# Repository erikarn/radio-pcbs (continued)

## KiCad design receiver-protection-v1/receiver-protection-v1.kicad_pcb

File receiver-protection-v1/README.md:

# SDR RX receiver protection

## What is this?

This is a super simple project to provide some level of protection
of an SDR receiver.

It adds surge protection, signal level clamping diodes and defaults
to shorting the receiver input when the power isn't applied.

I designed this to be able to leave in front of SDRs which may be
located near transmit antennas.  No, this won't protect your
SDR against a directly connected transmitter - ie, it's not a TX/RX
switch! - but it provides similar levels of protection as your
solid state HF/VHF/UHF transceiver may have.

## How to use it

 * Hook the input side up to your antenna
 * Hook the output side up to your SDR
 * Apply 12v to the supply pin
 * When you want to receive, apply 12v to the RX_EN pin
 * When you don't want to receive, don't apply 12v to the RX_EN pin

## Building it

 * Populate almost all the parts!
 * You don't need to populate two surge protectors - populate the D5
   one (on the input side) as that'll protect things before the relay.
 * Be careful of the Q1 footprint - yes, it's a small one

## Building modifications

If you don't need the relay switch and you just want the protection,
you can short pin 7 and 12 on the relay footprint (K1) and only populate
the SMA connectors, surge protectors and diodes.

If you want it to always be on when you apply power, then just short
pins 1 and 2 on J3 so 12v always appears on the RX_EN pin.

I supplied surge protector footprints on both sides of the relay.
You don't necessarily need both; I added it in case I wanted to
experiment.

## Notes!

### Using it with a bias-tee

 * Don't use this with an SDR that is providing a bias-tee; since it
   grounds the SDR facing port when RX_EN isn't enabled, it'll just short
   your bias-tee.
 * If you want to use it with a bias-tee then you can either clip pin 10
   of your relay or scrape away the pad/track on pin 10 of K1.  That way
   the SDR isn't grounded when RX_EN is off, and thus the bias-tee power
   isn't shorted.

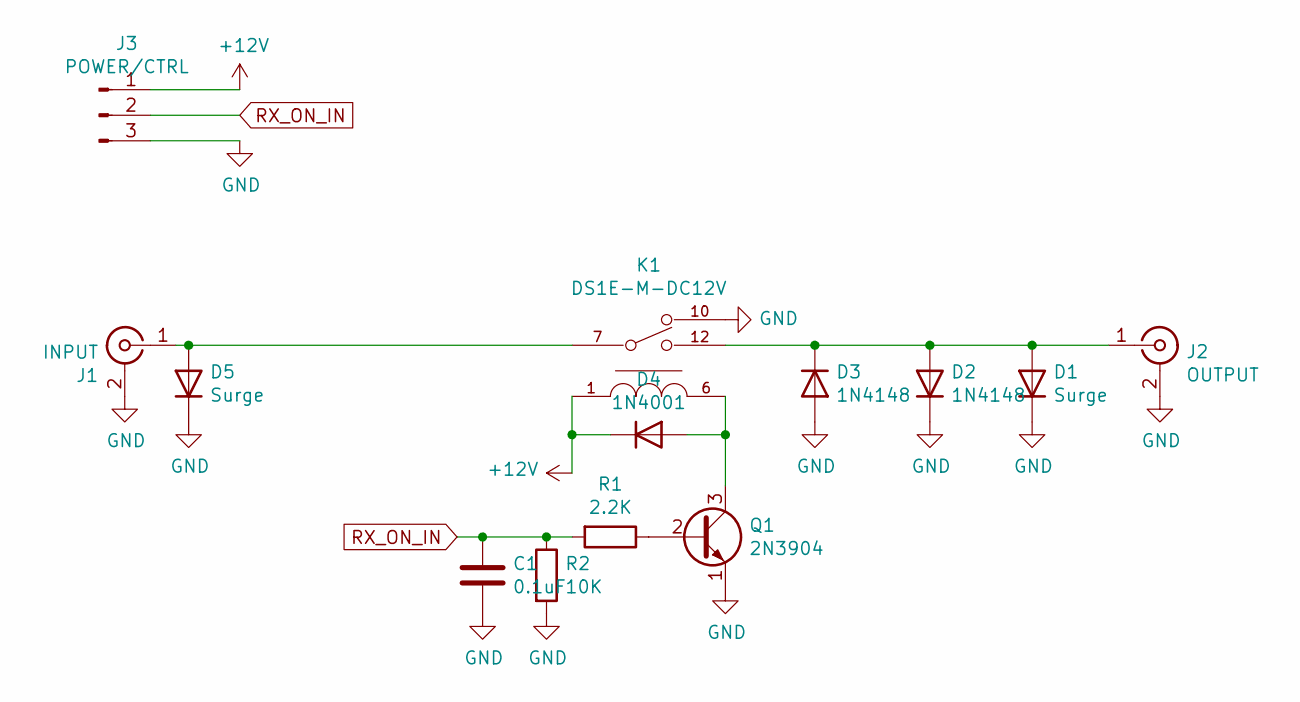
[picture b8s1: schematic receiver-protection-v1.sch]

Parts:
C1: 0.1uF; C_Disc_D3.8mm_W2.6mm_P2.50mm
D1, D5: Surge; D_DO-41_SOD81_P12.70mm_Horizontal
D2, D3: 1N4148; D_DO-35_SOD27_P7.62mm_Horizontal
D4: 1N4001; D_DO-41_SOD81_P12.70mm_Horizontal
J1: INPUT; SMA_Amphenol_132134-11_Vertical
J2: OUTPUT; SMA_Amphenol_132134-11_Vertical
J3: POWER/CTRL; PinHeader_1x03_P2.54mm_Vertical
K1: DS1E-M-DC12V; DIP-12_W7.62mm_Socket; current rating 3A; voltage rating AC 250V; mouser part number 769-DS1E-M-DC12V; digikey description RELAY GEN PURPOSE SPDT 2A 250V
Q1: 2N3904; TO-92_Inline
R1: 2.2K; R_Axial_DIN0207_L6.3mm_D2.5mm_P10.16mm_Horizontal
R2: 10K; R_Axial_DIN0207_L6.3mm_D2.5mm_P10.16mm_Horizontal

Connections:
+12V: D4.1 (K), J3.1, K1.1
GND: C1.2, D1.1 (K), D2.1 (K), D3.2 (A), D5.1 (K), J1.2 (Ext), J2.2 (Ext), J3.3, K1.10, Q1.1 (E), R2.2
unnamed: D1.2 (A), D2.2 (A), D3.1 (K), J2.1 (In), K1.12
unnamed: D4.2 (A), K1.6, Q1.3 (C)
unnamed: D5.2 (A), J1.1 (In), K1.7
unnamed: Q1.2 (B), R1.1
RX_ON_IN: C1.1, J3.2, R1.2, R2.1

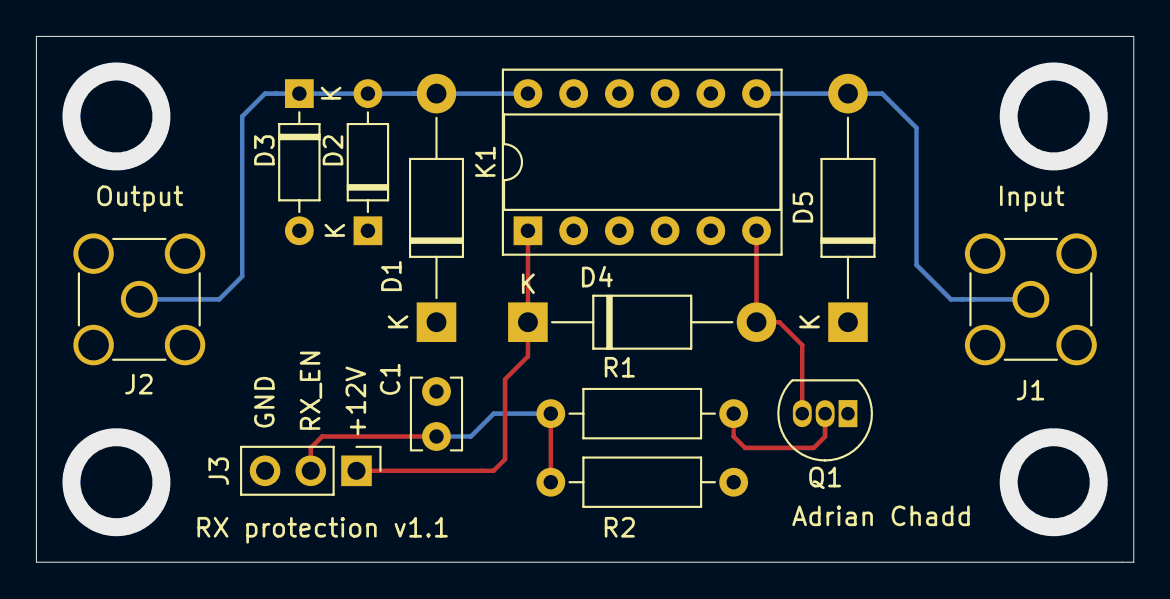
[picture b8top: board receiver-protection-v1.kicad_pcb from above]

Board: 2 copper layers, 61.0 x 29.2 mm, 13 parts (0 on the bottom side), 7 nets.

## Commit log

2020-09-14 Initial transverter control board prototype!
2020-09-22 ok, let's just put these in the top level
2020-09-22 Initial project - add basic receiver protection PCB.
    This is for protecting SDRs on receive antennas from being exposed
    whilst off, as well as some surge protection and signal-overload
    protection.
    I'll build it and sweep HF/VHF/UHF, see where it's useful.
2020-10-03 add revision 1.1 changes
    * make sure the mounting hole vias are attached to ground!
    * reverse input/output - make sure that the SDR facing output
    has the protection diodes and optional surge protector, and
    is grounded when the enable signal isn't applied
    * label input, output, power/ground/enable
    * add description, my name, and revision number
2020-10-03 v1.1 - whoops, annotate the schematic
2020-10-03 Add an initial readme!
2020-10-03 Add initial top-level readme
2020-11-16 initial coilcraft library thingy
2020-11-16 board for testing 630m filter designs
2020-11-16 WIP for ts-140 + pll-2001 PLL IC replacement adapter board
2020-11-16 WIP for a 630m TX/RX transverter control board - letting a TS-430S as a transverter control a 630m TX/RX path.
2020-12-11 Updates!
2020-12-12 Update PCB layout, it should work? kinda? we'll see.
2020-12-30 Whoops - my coil orientation/pinout was JUST PLAIN WRONG.
    So fix the schematic to do the right thing; I'll have to hack something on my
    development pcb to test that the filter actually works..
2020-12-31 more fixes:
    * missed ground plane ties for the signal connectors, whoops
    * add ground pins for the coils so they can be tied to ground
    * add label
2020-12-31 More v0.3 fixes -
    * fix the bloody signal routing for that middle IF coil, what was I thinking
    * don't use a cap to xverter-gnd; just tie them together and to ground
    That should be much better!
2021-01-13 * More layout fixes * Make the silk screen layer not actually terrible
2021-01-16 I got the fucking relay power backwards. WTAF.
2021-03-13 Add initial ubitx IF board design, from ubitx v6.
    This is aimed to be a copy of the dual direction IF amplifiers
    that are used in the ubitx radios. It's intended to be used
    as bidirectional IF amplifiers or two separate IF amplifiers.
    Anyway, this is the first bit.
2021-03-13 * whoops, use a proper ground * make txb/rxb a pair of pairs, in case they want to be wired/powered via two separate connections (ie, as independent IF amplifiers) rather than expecting TXB/RXB to be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
2021-03-14 * add net file * update an actual routed pcb, need to fix labels and put my name on it
2021-03-14 whoops! fix
2021-03-14 * Layout updates * Fix text labelling * Add my text bits here!
    This was sent to oshpark as 1.0 today for printing!
2021-03-15 WHOOPS - my last minute vias were err, wrong.
    THIS is now what's sent as v1.0 to print at oshpark!
2021-04-07 add component for the ubitx trifilar inductor they use.
2021-04-07 Add initial ubitx mixer/filter board.
    This is the mixer and filter stage used in each of the two conversion stages.
    My goal is that only the parts needed for a given stage are populated, rather
    than building two separate PCB layouts.
2021-06-12 Add initial unfinished apple-ii rom adapter thingy
2021-06-12 Incremental update! Maybe this'll work? :-)
2021-06-12 whoops, missed a connection!
2021-06-16 Initial cut (rev 0.1) of the 8t28 <-> 74ls245 adapter
2021-06-16 Move some silkscreen bits around to hopefully look better
2021-06-20 Update PCB layout - space the vias out a little more!
2021-07-02 Initial unfinished ram upgrade for pcjr
2021-07-02 Updates to actually make this work!
    It didn't work with this plugged in, ROM or not populated.
    * Wow, I screwed up the address line naming, whoops, that removes a short
    across two address lines so now the apple-ii will boot with this plugged
    in w/ the 74LS138 populated but ROMs in the normal ROM slots.
    * Wow, I fucked up the logic. The logic I chose plainly wouldn't work.
    Replace it with a pair of NAND gates and a NOR gate to implement the
2021-08-08 Rom adapter update
2021-08-21 More layout fixes
2021-08-21 Update schematic to reflect the changes
2021-08-21 Update schematic and board layout a bit, I still need to finish this!
2022-01-03 Add initial otrona attache power supply replacement board design.
    so far i have the shape of the PCB cuts done (minus fan), will add the
    mounting holes and then the parts placement next.
2022-03-12 [otrona] Update schematic, layout, part selection
    so far so good... now to print it out and see
2022-03-12 [samtec] another connector in the library
2022-05-16 [otrona] ok fine i routed the damned board
2022-05-30 Fix initial hole placings and board size, connector spacing
    I still may need to tweak the top/bottom of the board clearance
    but at least now this SHOULD work.
    Also fix the connector spacing, I got it super bloody wrong.
    I still need to fix the pad size on the ATX connector, le sigh.
2022-06-07 Final update before I printed it!
2023-12-19 start re-laying things out, after my previous board just didn't fit right.
2023-12-20 more layout changes
    i haven't put in the ground planes yet, but now all of the CPU board wiring is
    hopefully in the right place for it to reach.
2023-12-20 more layout changes, ground plane
2023-12-20 Change the version, ha
2024-07-22 [components] add zilog parts for kicad
2024-07-22 [components] more components.
2024-07-22 initial expansion hacks
2024-07-23 [pcw] more schematic updates!
    slowly but surely getting there!
2024-07-23 [pcw] more updates!
2024-07-28 footprints
2024-07-28 [pcw] a simplified video board; will poke at this some more soon
2024-07-28 [pcw] initial component placement
2025-08-09 initial buffer amplifier prototype test, v1.0
    This is lifted from the kenwood ts-440s output buffer amplifier
    on the IF board, which taps audio from the audio output before
    the AF VR control, and provides a fixed level audio output to the
    audio data output for things like digital modes.
    earlier radios like the TS-670, TS-430, etc don't have a dedicated
    13 pin accessory jack for digital modes and rig control. this board
2025-08-10 [components] add kicad 9.0 component
2025-08-10 [ubitx] trifilar footprint
